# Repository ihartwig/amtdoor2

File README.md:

amtdoor2
========

This repository tracks files for AMT Door 2, an RFID based lock system in use at the [Ace Monster Toys](http://acemonstertoys.org/) hackspace in Oakland, CA. A complete description of the system these files are part of, [see the description on the AMT Wiki](http://wiki.acemonstertoys.org/Door#AMT_Door_2).

Included files:
* authCode - code to run on a raspberry pi or similar auth server
* housing - 2D drawings for assembly of the door tag reader
* hwTestCode - simplified panel mcu code to test clock settings
* panelMcuCode - firmware to run on the panel mcu that interprets RFID signals and accepts opening requests from the auth server
* physical - Eagle schematic/boards for the panel mcu

## Setting up on a 16u4:

to flash a new atmega16u4 for this code using an ISP (without the bootloader):

```
$ avrdude -p atmega16u4 -P usb -c avrispmkii -u -U lfuse:w:0xfc:m -U hfuse:w:0xd0:m -U efuse:w:0xc3:m
$ make MCU=atmega16u4
$ avrdude -p atmega16u4 -P usb -c avrispmkii -U flash:w:main.hex
```

to load the bootloader first using an ISP:

```
need to set fuses. we will copy from adafruit atmega32u4 dev board.
adafruit sets to: (E:C3, H:D0, L:FC) (avrdude-- has a typo)

Extended (0 is set):
7 1 Reserved
  1 Reserved
  0 Reserved
  0 Reserved
  0 HWBE          Hardware Boot Enable
  0 BODLEVEL2(1)  Brown-out Detector trigger level
  1 BODLEVEL1(1)  Brown-out Detector trigger level
0 1 BODLEVEL0(1)  Brown-out Detector trigger level

High (0 is set):
7 1 OCDEN         Enable OCD
  1 JTAGEN        Enable JTAG
  0 SPIEN         Enable Serial Program and Data Downloading
  1 WDTON         Watchdog Timer always on
  0 EESAVE        EEPROM memory is preserved through the Chip Erase
  0 BOOTSZ1       Select Boot Size (see Table 28-7 for details)
  0 BOOTSZ0       Select Boot Size (see Table 28-7 for details)
0 0 BOOTRST       Select Bootloader Address as Reset Vector

Low (0 is set):
7 1 CKDIV8        Divide clock by 8
  1 CKOUT         Clock output
  1 SUT1          Select start-up time
  1 SUT0          Select start-up time
  1 CKSEL3        Select Clock source
  1 CKSEL2        Select Clock source
  0 CKSEL1        Select Clock source
0 0 CKSEL0        Select Clock source
```

to compile CDC bootloader (from lufa-lib trunk):
for BOOTSZ1 = BOOTSZ0 = 0. see datasheet table 27-8.

```
$ make MCU=atmega16u4 BOOT_START=0x1800 F_CPU=16000000
$ mv BootloaderCDC.hex BootloaderCDC_16u4.hex
$ avrdude -p atmega16u4 -P usb -c avrispmkii -U flash:w:BootloaderCDC_16u4.hex
```

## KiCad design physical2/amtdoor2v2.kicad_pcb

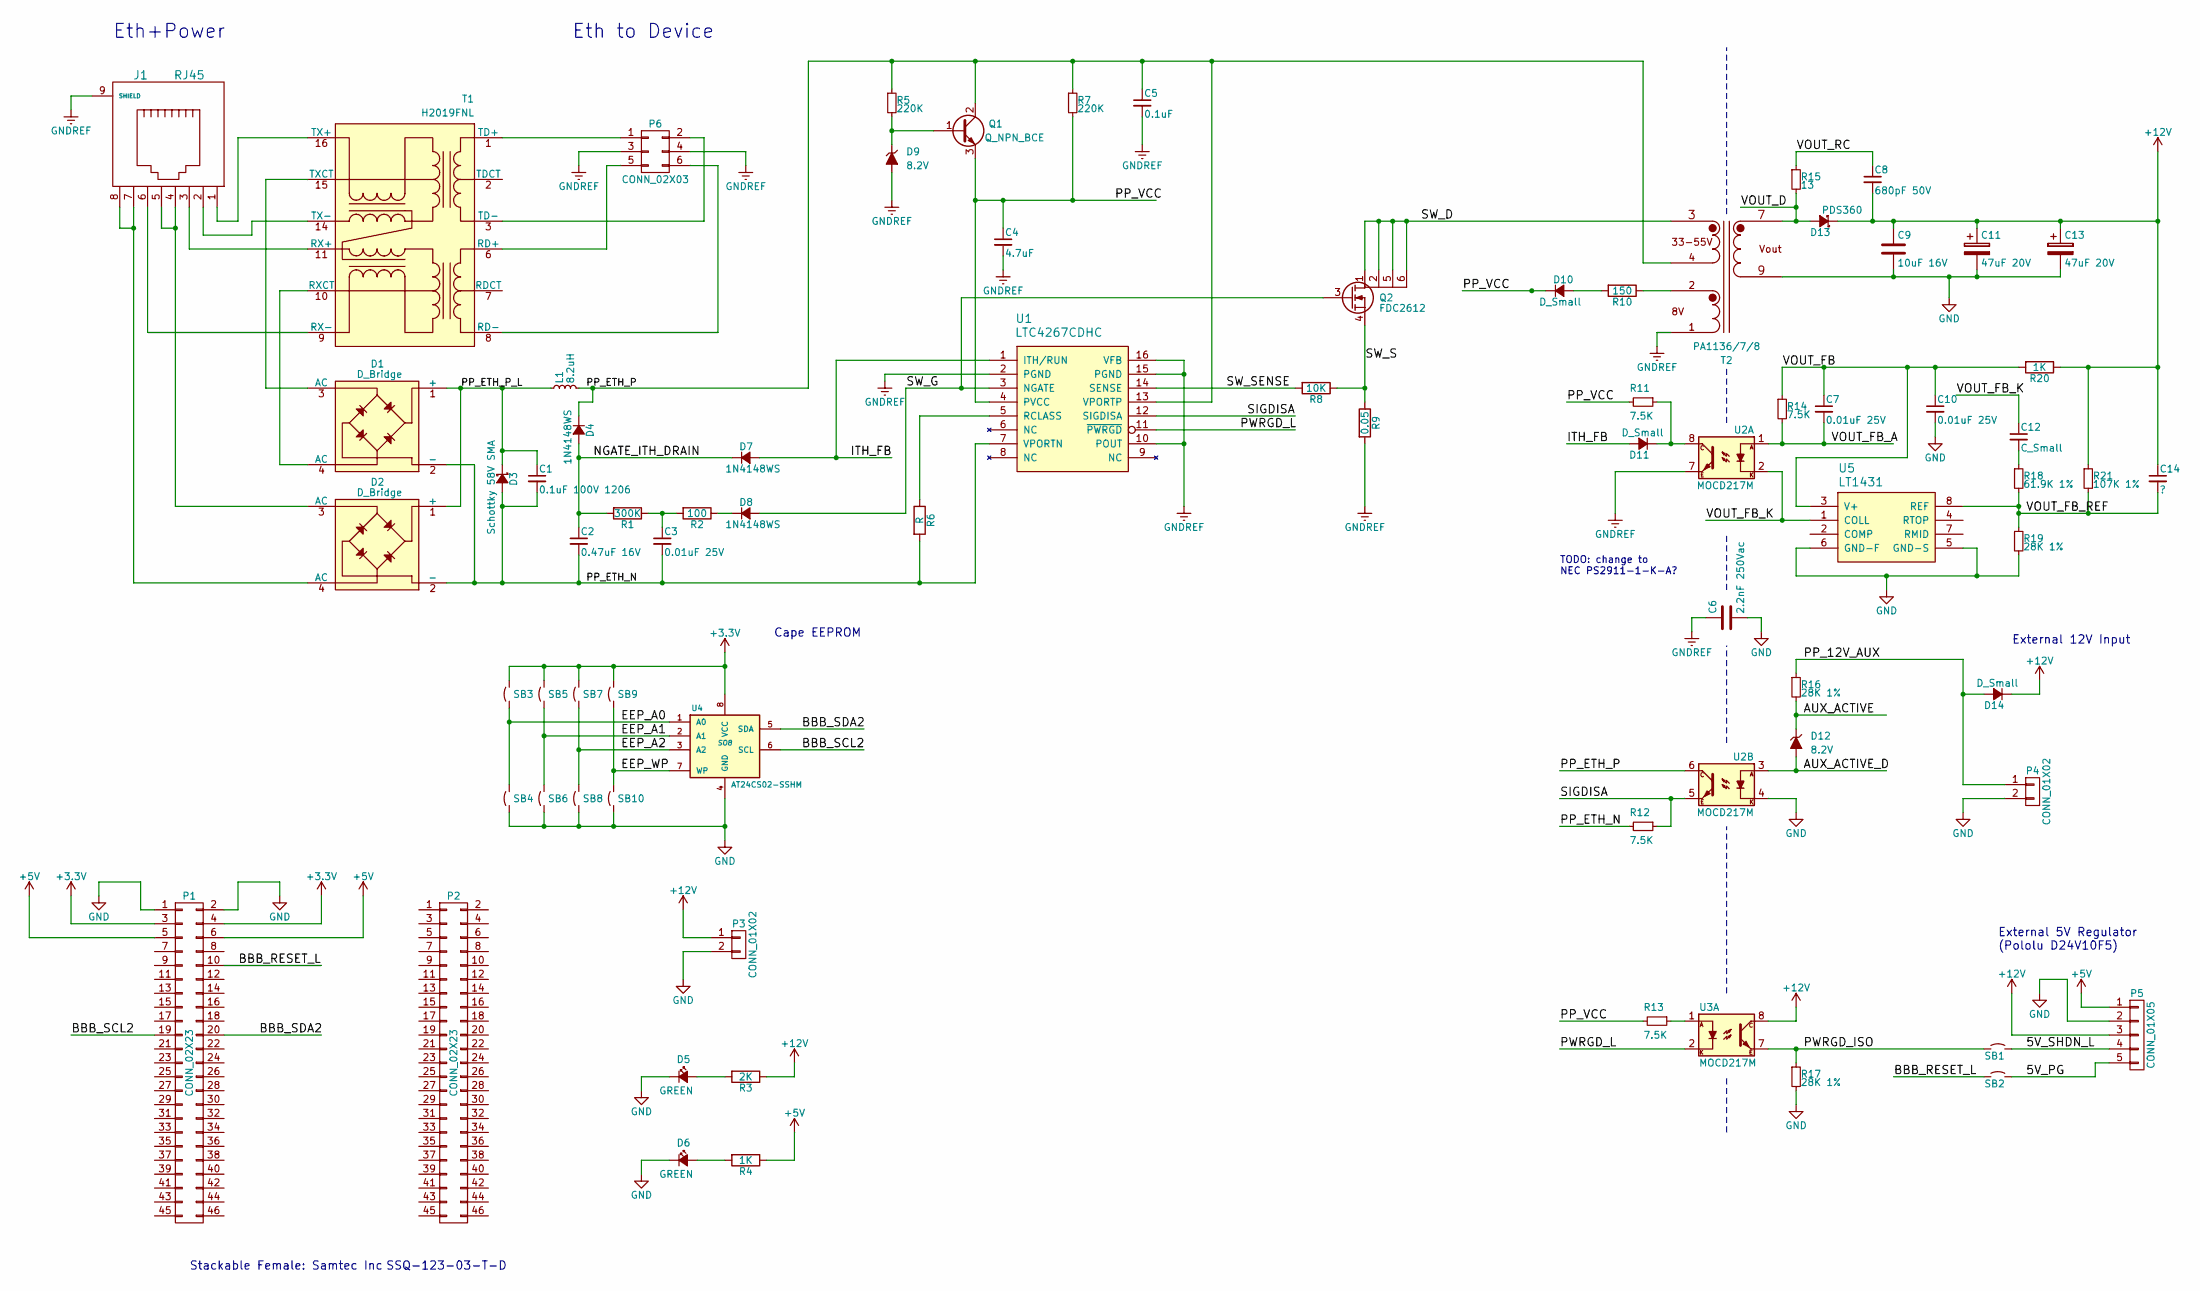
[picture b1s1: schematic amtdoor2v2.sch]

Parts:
C1: 0.1uF 100V 1206
C2: 0.47uF 16V
C3, C7, C10: 0.01uF 25V
C4: 4.7uF
C5: 0.1uF
C6: 2.2nF 250Vac
C8: 680pF 50V
C9: 10uF 16V
C11, C13: 47uF 20V
C12: C_Small
C14: ?
D1, D2: D_Bridge
D3: Schottky 58V SMA
D4, D7, D8: 1N4148WS
D5, D6: GREEN
D9, D12: 8.2V
D10, D11, D14: D_Small
D13: PDS360
J1: RJ45
L1: 8.2uH
P1, P2: CONN_02X23
P3, P4: CONN_01X02
P5: CONN_01X05
P6: CONN_02X03
Q1: Q_NPN_BCE
Q2: FDC2612
R1: 300K
R2: 100
R3: 2K
R4, R20: 1K
R5, R7: 220K
R6: R
R8: 10K
R9: 0.05
R10: 150
R11, R12, R13, R14: 7.5K
R15: 13
R16, R17, R19: 28K 1%
R18: 61.9K 1%
R21: 107K 1%
SB1, SB2, SB3, SB4, SB5, SB6, SB7, SB8, SB9, SB10: SolderBridge
T1: H2019FNL
T2: PA1136/7/8
U1: LTC4267CDHC
U2, U3: MOCD217M
U4: AT24CS02-SSHM; SO8
U5: LT1431

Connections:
+3V3: P1.3, P1.4, SB3.1, SB5.1, SB7.1, SB9.1, U4.8 (VCC)
+5V: P1.5, P1.6, P5.1, R4.1
+12V: C8.2, C9.1, C11.1, C13.1, C14.1, D13.1 (K), D14.1 (K), P3.1, P5.3, R3.1, R20.1, R21.1, U3.8
/5V_PG: P5.5, SB2.1
/5V_SHDN_L: P5.4, SB1.1
/AUX_ACTIVE: D12.1 (K), R16.2
/AUX_ACTIVE_D: D12.2 (A), U2.3
/BBB_RESET_L: P1.10, SB2.2
/BBB_SCL2: P1.19, U4.6 (SCL)
/BBB_SDA2: P1.20, U4.5 (SDA)
/EEP_A0: SB3.2, SB4.1, U4.1 (A0)
/EEP_A1: SB5.2, SB6.1, U4.2 (A1)
/EEP_A2: SB7.2, SB8.1, U4.3 (A2)
/EEP_WP: SB9.2, SB10.1, U4.7 (WP)
/ITH_FB: D7.2 (A), D11.2 (A), U1.1 (ITH/RUN)
/NGATE_ITH_DRAIN: C2.1, D4.2 (A), D7.1 (K), R1.2
/PP_12V_AUX: D14.2 (A), P4.1, R16.1
/PP_ETH_N: C1.2, C2.2, C3.2, D1.2 (-), D2.2 (-), D3.2 (A), R6.2, R12.2, U1.7 (VPORTN)
/PP_ETH_P: C5.1, D4.1 (K), L1.2, Q1.2 (C), R5.1, R7.1, T2.4 (SRC2), U1.13 (VPORTP), U2.6
/PP_ETH_P_L: C1.1, D1.1 (+), D2.1 (+), D3.1 (K), L1.1
/PP_VCC: C4.1, D10.1 (K), Q1.3 (E), R7.2, R11.2, R13.2, U1.4 (PVCC)
/PWRGD_ISO: R17.1, SB1.2, U3.7
/PWRGD_L: U1.11 (~PWRGD), U3.2
/SIGDISA: R12.1, U1.12 (SIGDISA), U2.5
/SW_D: Q2.1 (D1), Q2.2 (D2), Q2.5 (D3), Q2.6 (D4), T2.3 (SRC1)
/SW_G: D8.2 (A), Q2.3 (G), U1.3 (NGATE)
/SW_S: Q2.4 (S), R8.1, R9.1
/SW_SENSE: R8.2, U1.14 (SENSE)
/VOUT_D: D13.2 (A), R15.2, T2.7 (OUT1)
/VOUT_FB: C7.1, C10.1, R14.1, R20.2, U5.3 (V+)
/VOUT_FB_A: C7.2, R14.2, U2.1
/VOUT_FB_K: C12.1, U2.2, U5.1 (COLL)
/VOUT_FB_REF: C14.2, R18.2, R19.1, R21.2, U5.8 (REF)
/VOUT_RC: C8.1, R15.1
GND: C6.2, C9.2, C10.2, C11.2, C13.2, D5.1 (K), D6.1 (K), P1.1, P1.2, P3.2, P4.2, P5.2, R17.2, R19.2, SB4.2, SB6.2, SB8.2, SB10.2, T2.9 (OUT2), U2.4, U4.4 (GND), U5.5 (GND-S), U5.6 (GND-F)
GNDREF: C4.2, C5.2, C6.1, D9.2 (A), J1.9 (SHIELD), P6.3, P6.4, R9.2, T2.1 (FB2), U1.2 (PGND), U1.10 (POUT), U1.15 (PGND), U1.16 (VFB), U2.7
unnamed: C3.1, R1.1, R2.2
unnamed: C12.2, R18.1
unnamed: D1.3 (AC), T1.15 (TXCT)
unnamed: D1.4 (AC), T1.10 (RXCT)
unnamed: D2.3 (AC), J1.4, J1.5
unnamed: D2.4 (AC), J1.7, J1.8
unnamed: D5.2 (A), R3.2
unnamed: D6.2 (A), R4.2
unnamed: D8.1 (K), R2.1
unnamed: D9.1 (K), Q1.1 (B), R5.2
unnamed: D10.2 (A), R10.2
unnamed: D11.1 (K), R11.1, U2.8
unnamed: J1.1, T1.16 (TX+)
unnamed: J1.2, T1.14 (TX-)
unnamed: J1.3, T1.11 (RX+)
unnamed: J1.6, T1.9 (RX-)
unnamed: P6.1, T1.1 (TD+)
unnamed: P6.2, T1.3 (TD-)
unnamed: P6.5, T1.6 (RD+)
unnamed: P6.6, T1.8 (RD-)
unnamed: R6.1, U1.5 (RCLASS)
unnamed: R10.1, T2.2 (FB1)
unnamed: R13.1, U3.1

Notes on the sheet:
Eth+Power
Eth to Device
TODO: change to NEC PS2911-1-K-A?
Stackable Female: Samtec Inc SSQ-123-03-T-D
External 5V Regulator (Pololu D24V10F5)
External 12V Input
Cape EEPROM

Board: 2 copper layers, 76 parts (9 on the bottom side), 59 nets, no tracks yet.

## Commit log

2014-05-31 attempt to ignore extra eagle files
2014-05-31 add rev 1 of controller and usb-rj45 breakout boards
2014-05-31 add external panel laser files
2014-06-01 update gitignore for micro programs
2014-06-01 add LUFA lib and skeleton code to start a virtual serial port
2014-06-04 implement virtual serial echo
2014-06-06 enough code to read the tag results back to computer
2014-06-06 code to parse and report tag
2014-06-08 implemented 1ms system timer
2014-06-08 support for authenticating and opening the door
2014-07-12 record debugging info on bootloading the 16u4
2014-07-13 add hw test and auth (raspberry pi/shevaplug) code
2014-07-13 add auto-run scripts
2014-07-13 update auth script paths. new setup script.
2014-07-13 chmod 755 door_test.sh in repo
2014-07-13 oops. fix missing $
2014-07-27 fix relay pin assignments. remove debug statements.
2014-07-27 tweak relay pulse length
2014-07-27 disable second led by default to conserve power/reduce thermal load on ldo
2014-07-27 rework the auth code files to auto-restart the door test check
2014-07-28 add auth code removal instructions
2014-07-28 push all doortestd output to log
2014-07-28 push all doortestd output to log (again)
2014-07-28 push all doortestd output to log (again again)
2014-07-28 push all doortestd output to log (again again again)
2014-08-07 add USB tests
2014-08-09 add new laser files for panel mcu (since this can't be outside)
2014-08-09 new auto-lock code
2014-10-20 update readme to point to new wiki page
2014-10-20 fix readme typo
2015-07-01 initial kicad project
2015-07-28 First major schematic/lib release. No board.
    - Add supporting docs for LTC4267/PoE circuit
    - Implement LTC4267-DC1145BF 12V PoE circuit
    - Add BeagleBone Black headers and docs
    - Add BBB cape required eeprom
    - Add necessary parts (H2019, LTC4267, LT1431, etc)
    - Updated netlist
2015-08-02 Fix PoE schematic, make major footprints, begin board grouping.
    * Swap RJ45 output for 2x3 .1" header. Use either small pcb or custom cable to connect to BBB.
    * Add footprints for ethernet jacks, transformers, large diodes/inductors, optoisolators, solder bridge.
    * Fix direction of optoisolator in feedback.
    * Fix power nFET symbol.
    * Fix incorrect ground on RJ45 shields.
    * Build symbol <-> footprint cmp file.
2016-09-11 fix panelMcuCode not reading the latest rfid tag
    The Parallax RFID reader sends tags of value XXXXXXXX in the format "\nXXXXXXXX\r". Since we handled \r\n by ignoring \r and reading \n we always left the most recent tag in the buffer. Now we read t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
2016-10-18 update panelmcu makefile for usbasp programmer
